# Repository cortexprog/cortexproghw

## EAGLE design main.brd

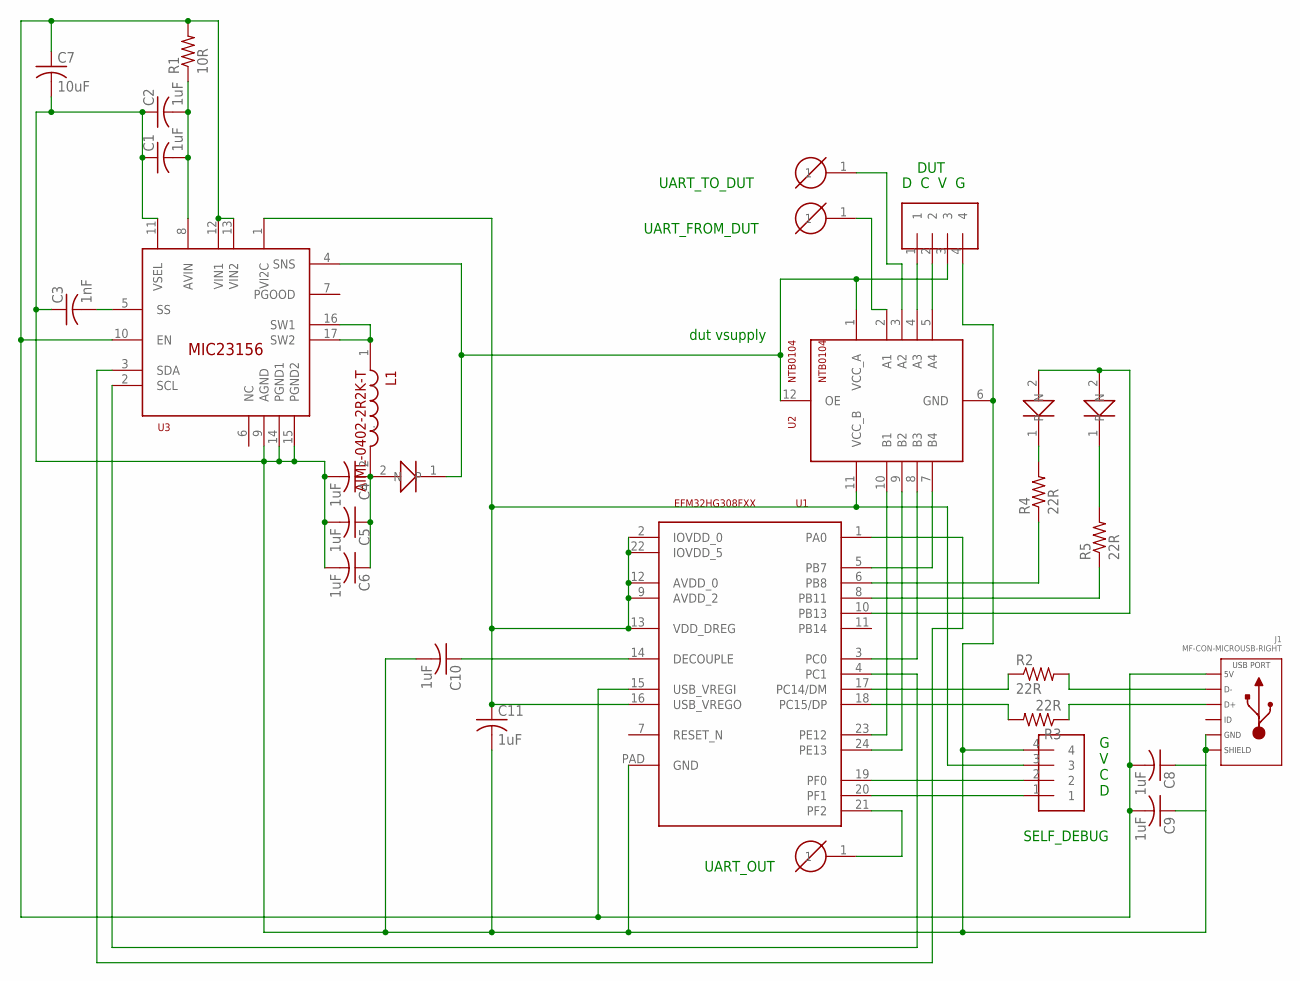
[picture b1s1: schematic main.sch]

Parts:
C1, C2, C4, C5, C6, C8, C9, C10, C11: 1uF; C0402K
C3: 1nF; C0402K
C7: 10uF; C1206K
CN_RX: PTH_PIN
CN_TX: PTH_PIN
CONN_OUT: PIN_HEADER_4X1POLARIZED; PIN_HEADER_4X1_POLARIZED
CONN_SELF: PIN_HEADER_4X1POLARIZED; PIN_HEADER_4X1_POLARIZED
D1-PWR, D2-ACT: LED0805; 0805
D3: TS4148; 0805
J1: MF-CON-MICROUSB-RIGHT; MICROUSB-RIGHT
L1: AIML-0402-2R2K-T; 0402
R1: 10R; R0402
R2, R3, R4, R5: 22R; R0402
TP_UART_OUT: PTH_PIN
U1: EFM32HG308FXX; QFN26-0.65
U2: NTB0104; XQFN12
U3: MIC23156; MLF17-2.8X2.5MM

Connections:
DEBUG_UART_DI: U1.23 (PE12), U2.10 (B1)
DEBUG_UART_DO: U1.24 (PE13), U2.9 (B2)
DUT_SWDCK: CONN_OUT.2, U2.5 (A4)
DUT_SWDIO: CONN_OUT.1, U2.4 (A3)
DUT_VREF: CONN_OUT.3, D3.1 (N), U2.1 (VCC_A), U2.12 (OE), U3.4 (SNS)
GND: C1.1, C2.1, C3.1, C4.2, C5.2, C6.2, C7.2, C8.1, C9.1, C10.2, C11.2, CONN_OUT.4, CONN_SELF.4, J1.5 (GND), J1.S1 (SLD), J1.S2 (SLD), J1.S3 (SLD), J1.S4 (SLD), J1.S5 (SLD), J1.S6 (SLD), U1.PAD (GND), U2.6 (GND), U3.9 (AGND), U3.11 (VSEL), U3.14 (PGND1), U3.15 (PGND2)
LED_ACT_1: R5.1, U1.8 (PB11)
LED_COMMON: D1-PWR.2, D2-ACT.2, U1.10 (PB13)
LED_PWR_1: R4.1, U1.6 (PB8)
unnamed: C10.1, U1.14 (DECOUPLE)
unnamed: L1.1 (.), U3.16 (SW1), U3.17 (SW2)
unnamed: C1.2, C2.2, R1.1, U3.8 (AVIN)
unnamed: TP_UART_OUT.1, U1.21 (PF2)
unnamed: C4.1, C5.1, C6.1, D3.2, L1.2 (..)
unnamed: D2-ACT.1 (N), R5.2
unnamed: D1-PWR.1 (N), R4.2
unnamed: C3.2, U3.5 (SS)
OUT_SWDCK: U1.5 (PB7), U2.7 (B4)
OUT_SWDIO: U1.3 (PC0), U2.8 (B3)
SCL: U1.4 (PC1), U3.2 (SCL)
SDA: U1.1 (PA0), U3.3 (SDA)
SELF_SWDCK: CONN_SELF.2, U1.19 (PF0)
SELF_SWDIO: CONN_SELF.1, U1.20 (PF1)
UART_RX_FROM_DUT: CN_RX.1, U2.2 (A1)
UART_TX_TO_DUT: CN_TX.1, U2.3 (A2)
USB_DM: R2.1, U1.17 (PC14/DM)
USB_DM_1: J1.2 (D-), R2.2
USB_DP: R3.2, U1.18 (PC15/DP)
USB_DP_1: J1.3 (D+), R3.1
VBUS: C7.1, C8.2, C9.2, J1.1 (5V), R1.2, U1.15 (USB_VREGI), U3.10 (EN), U3.12 (VIN1), U3.13 (VIN2)
VCC_3V3: C11.1, CONN_SELF.3, U1.2 (IOVDD_0), U1.9 (AVDD_2), U1.12 (AVDD_0), U1.13 (VDD_DREG), U1.16 (USB_VREGO), U1.22 (IOVDD_5), U2.11 (VCC_B), U3.1 (VI2C)

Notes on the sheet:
G V C D
D C V G
SELF_DEBUG
DUT
UART_TO_DUT
UART_FROM_DUT
UART_OUT
dut vsupply

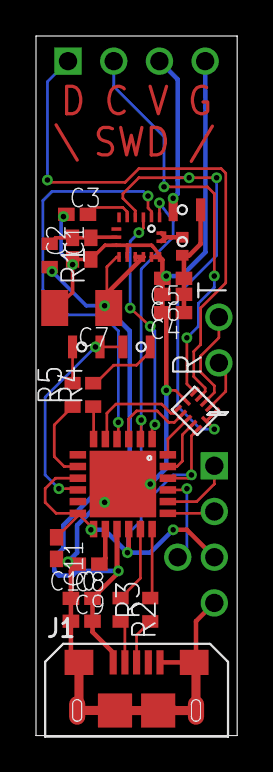
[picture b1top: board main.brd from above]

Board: 2 copper layers, 11.2 x 38.9 mm, 29 parts (0 on the bottom side), 31 nets.
